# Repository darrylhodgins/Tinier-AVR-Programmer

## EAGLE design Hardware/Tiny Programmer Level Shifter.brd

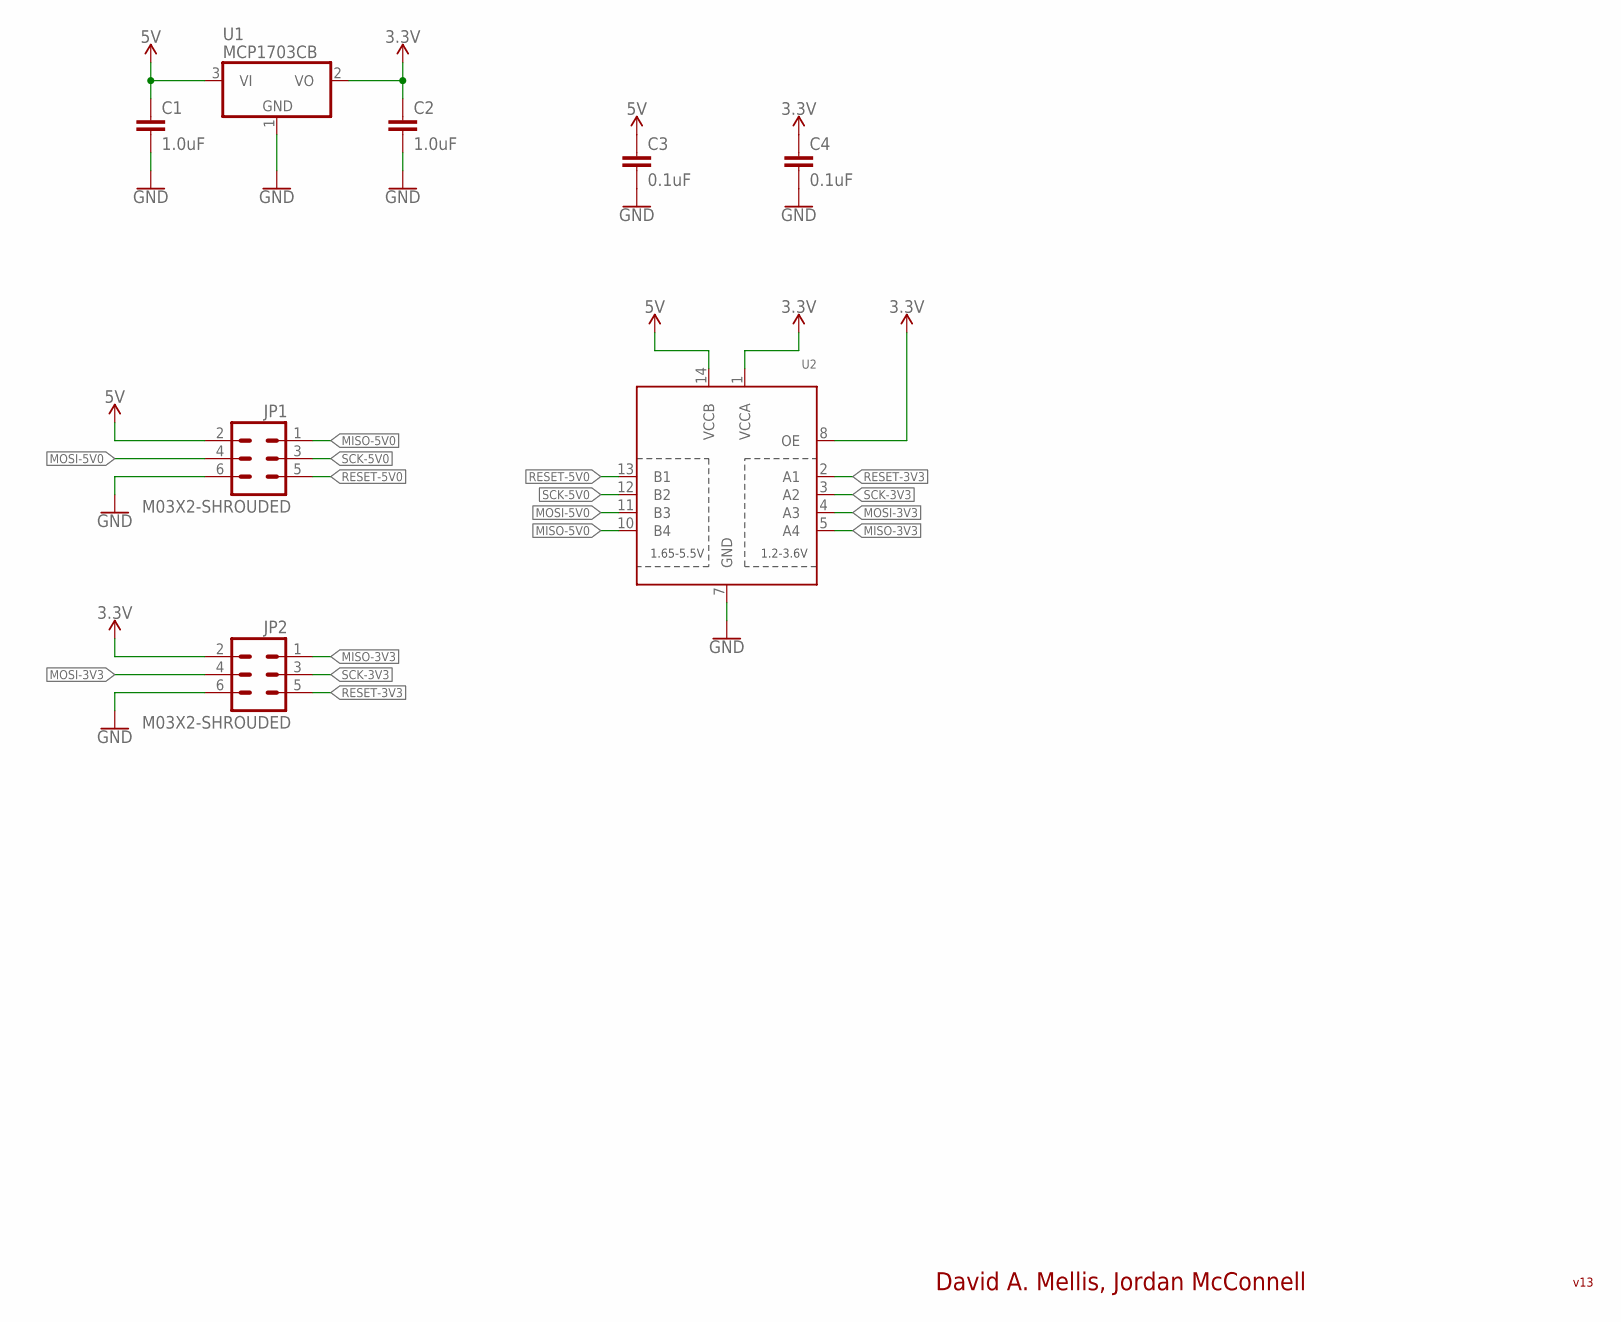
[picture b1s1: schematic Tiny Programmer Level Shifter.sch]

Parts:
C1, C2: 1.0uF; 0603-CAP
C3, C4: 0.1uF; 0603-CAP
JP1, JP2: M03X2-SHROUDED; 2X3-SHROUDED-B
U1: MCP1703CB; SOT23
U2: TXB0104PWR; TSSOP14

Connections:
3.3V: C2.1, C4.1, JP2.2, U1.2 (VO), U2.1 (VCCA), U2.8 (OE)
5V: C1.1, C3.1, JP1.2, U1.3 (VI), U2.14 (VCCB)
GND: C1.2, C2.2, C3.2, C4.2, JP1.6, JP2.6, U1.1 (GND), U2.7 (GND)
MISO-3V3: JP2.1, U2.5 (A4)
MISO-5V0: JP1.1, U2.10 (B4)
MOSI-3V3: JP2.4, U2.4 (A3)
MOSI-5V0: JP1.4, U2.11 (B3)
RESET-3V3: JP2.5, U2.2 (A1)
RESET-5V0: JP1.5, U2.13 (B1)
SCK-3V3: JP2.3, U2.3 (A2)
SCK-5V0: JP1.3, U2.12 (B2)

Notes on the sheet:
David A. Mellis, Jordan McConnell
v13

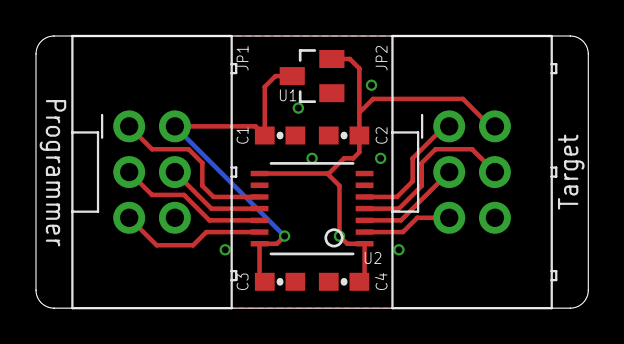
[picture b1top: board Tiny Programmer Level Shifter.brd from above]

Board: 2 copper layers, 30.7 x 15.1 mm, 8 parts (0 on the bottom side), 11 nets.

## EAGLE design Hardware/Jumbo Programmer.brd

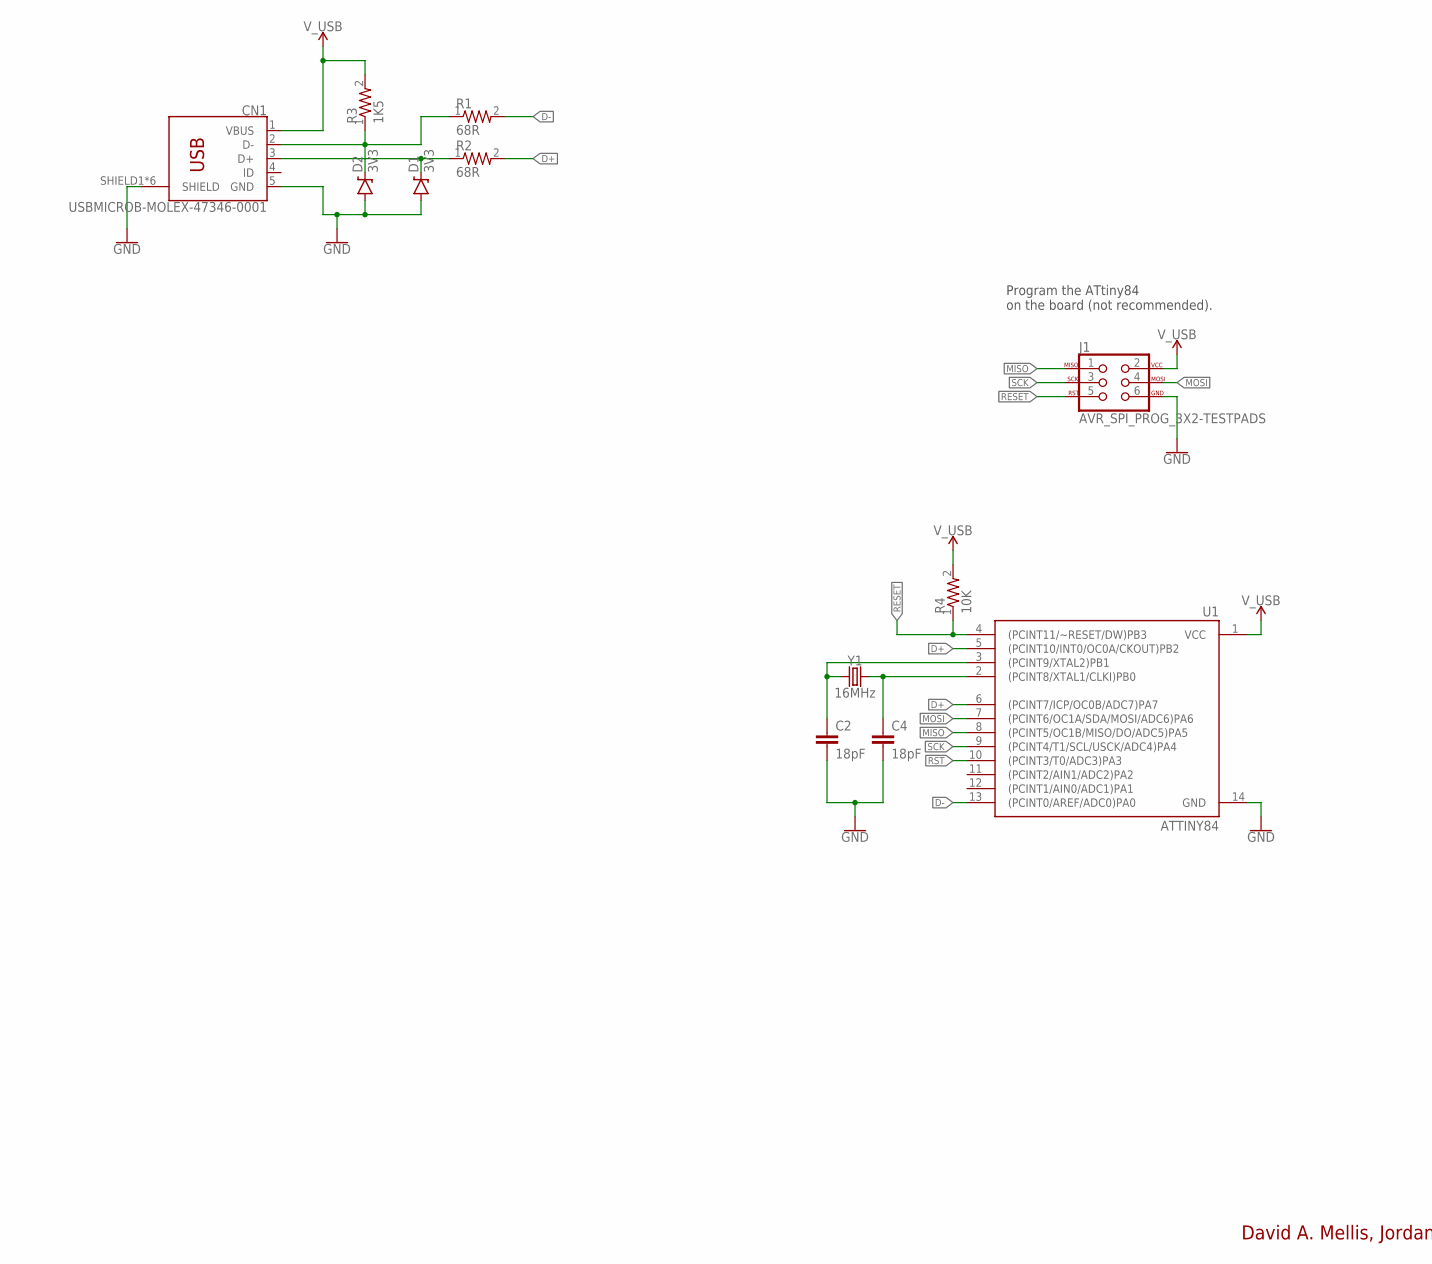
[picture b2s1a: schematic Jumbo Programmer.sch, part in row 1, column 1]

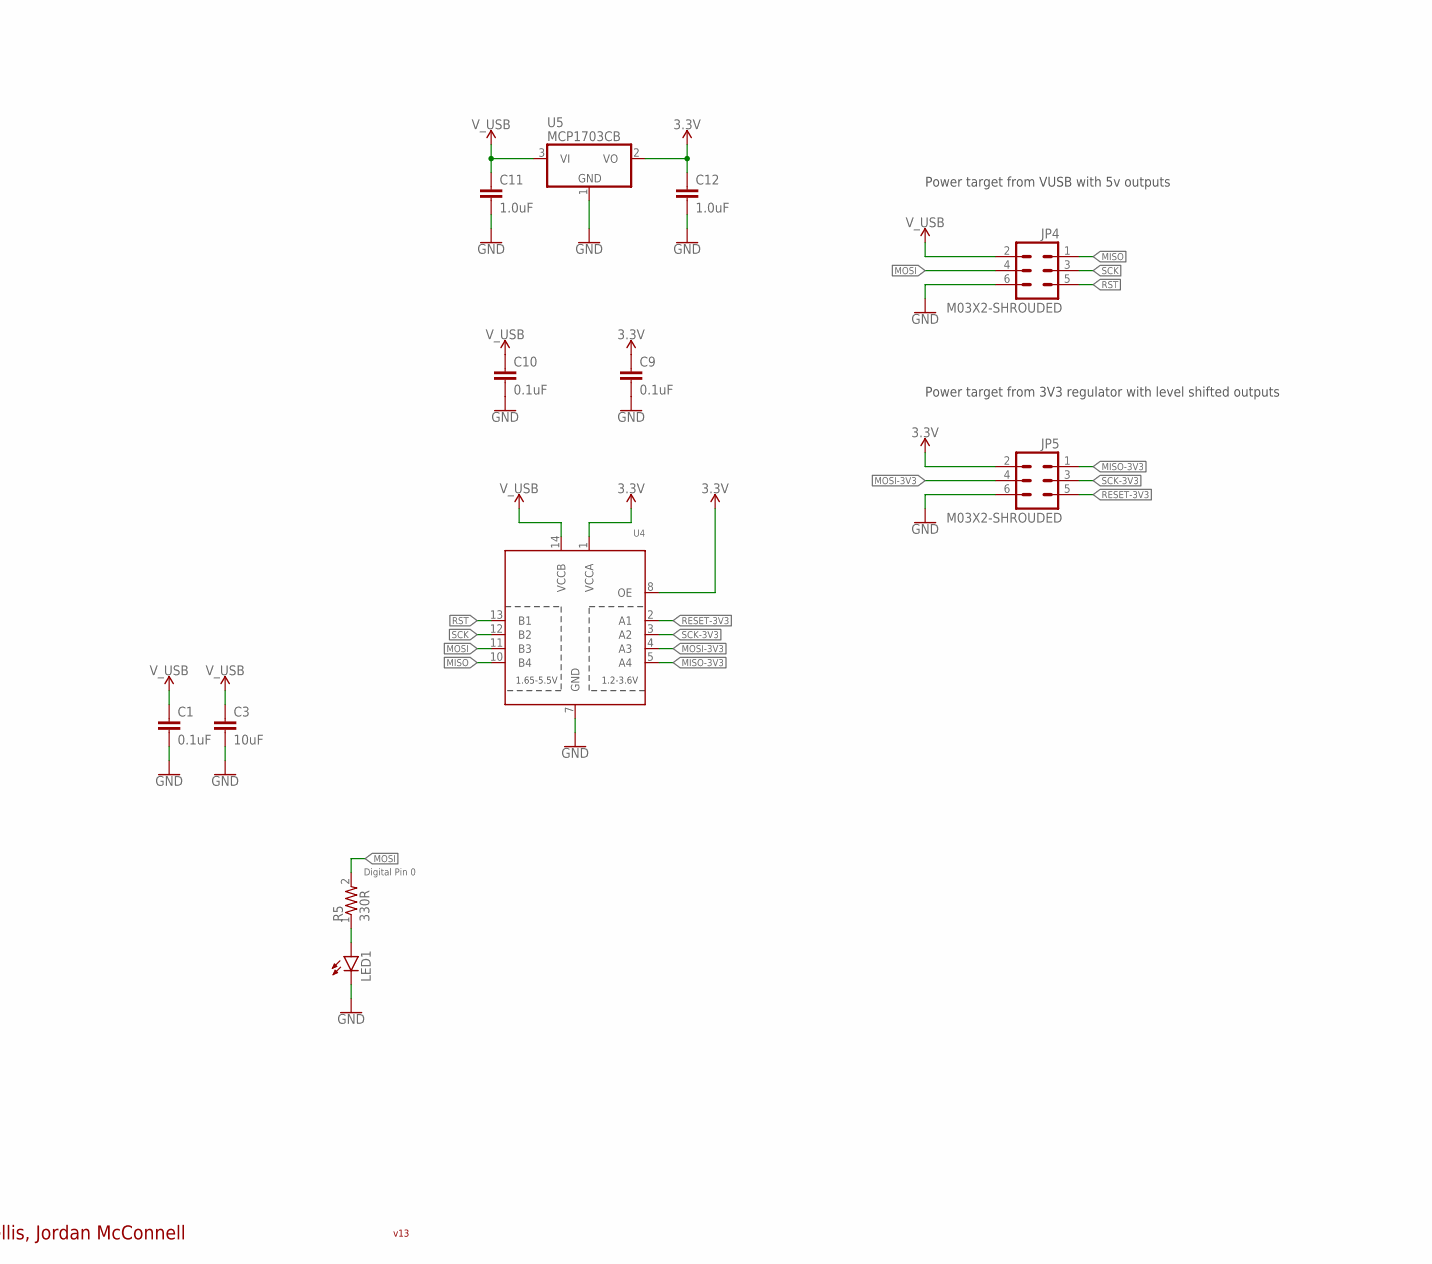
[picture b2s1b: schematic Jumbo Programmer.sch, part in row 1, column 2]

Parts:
C1, C9, C10: 0.1uF; 0603-CAP
C2, C4: 18pF; 0603-CAP
C3: 10uF; 0603-CAP
C11, C12: 1.0uF; 0603-CAP
CN1: USBMICROB-MOLEX-47346-0001; MOLEX_47346-0001
D1, D2: 3V3; SOD-323
J1: AVR_SPI_PROG_3X2-TESTPADS; 2X3_TEST_PADS
JP4, JP5: M03X2-SHROUDED; 2X3-SHROUDED-B
LED1: LED0603; LED-0603
R1, R2: 68R; 0603-RES
R3: 1K5; 0603-RES
R4: 10K; 0603-RES
R5: 330R; 0603-RES
U1: ATTINY84; SO14
U4: TXB0104PWR; TSSOP14
U5: MCP1703CB; SOT23
Y1: 16MHz; CRYSTAL-SMD-5X3.2-4PAD

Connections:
3.3V: C9.1, C12.1, JP5.2, U4.1 (VCCA), U4.8 (OE), U5.2 (VO)
D+: R2.2, U1.5 ((PCINT10/INT0/OC0A/CKOUT)PB2), U1.6 ((PCINT7/ICP/OC0B/ADC7)PA7)
D-: R1.2, U1.13 ((PCINT0/AREF/ADC0)PA0)
GND: C1.2, C2.2, C3.2, C4.2, C9.2, C10.2, C11.2, C12.2, CN1.5 (GND), CN1.SHIELD1 (SHIELD), CN1.SHIELD2 (SHIELD), CN1.SHIELD3 (SHIELD), CN1.SHIELD4 (SHIELD), CN1.SHIELD5 (SHIELD), CN1.SHIELD6 (SHIELD), D1.A, D2.A, J1.6, JP4.6, JP5.6, LED1.C, U1.14 (GND), U4.7 (GND), U5.1 (GND)
MISO: J1.1, JP4.1, U1.8 ((PCINT5/OC1B/MISO/DO/ADC5)PA5), U4.10 (B4)
MISO-3V3: JP5.1, U4.5 (A4)
MOSI: J1.4, JP4.4, R5.2, U1.7 ((PCINT6/OC1A/SDA/MOSI/ADC6)PA6), U4.11 (B3)
MOSI-3V3: JP5.4, U4.4 (A3)
unnamed: CN1.2 (D-), D2.C, R1.1, R3.1
unnamed: CN1.3 (D+), D1.C, R2.1
unnamed: C2.1, U1.3 ((PCINT9/XTAL2)PB1), Y1.1
unnamed: C4.1, U1.2 ((PCINT8/XTAL1/CLKI)PB0), Y1.3 (2)
unnamed: LED1.A, R5.1
RESET: J1.5, R4.1, U1.4 ((PCINT11/~RESET/DW)PB3)
RESET-3V3: JP5.5, U4.2 (A1)
RST: JP4.5, U1.10 ((PCINT3/T0/ADC3)PA3), U4.13 (B1)
SCK: J1.3, JP4.3, U1.9 ((PCINT4/T1/SCL/USCK/ADC4)PA4), U4.12 (B2)
SCK-3V3: JP5.3, U4.3 (A2)
V_USB: C1.1, C3.1, C10.1, C11.1, CN1.1 (VBUS), J1.2, JP4.2, R3.2, R4.2, U1.1 (VCC), U4.14 (VCCB), U5.3 (VI)

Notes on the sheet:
David A. Mellis, Jordan McConnell
Digital Pin 0
Program the ATtiny84 on the board (not recommended).
v13
Power target from VUSB with 5v outputs
Power target from 3V3 regulator with level shifted outputs

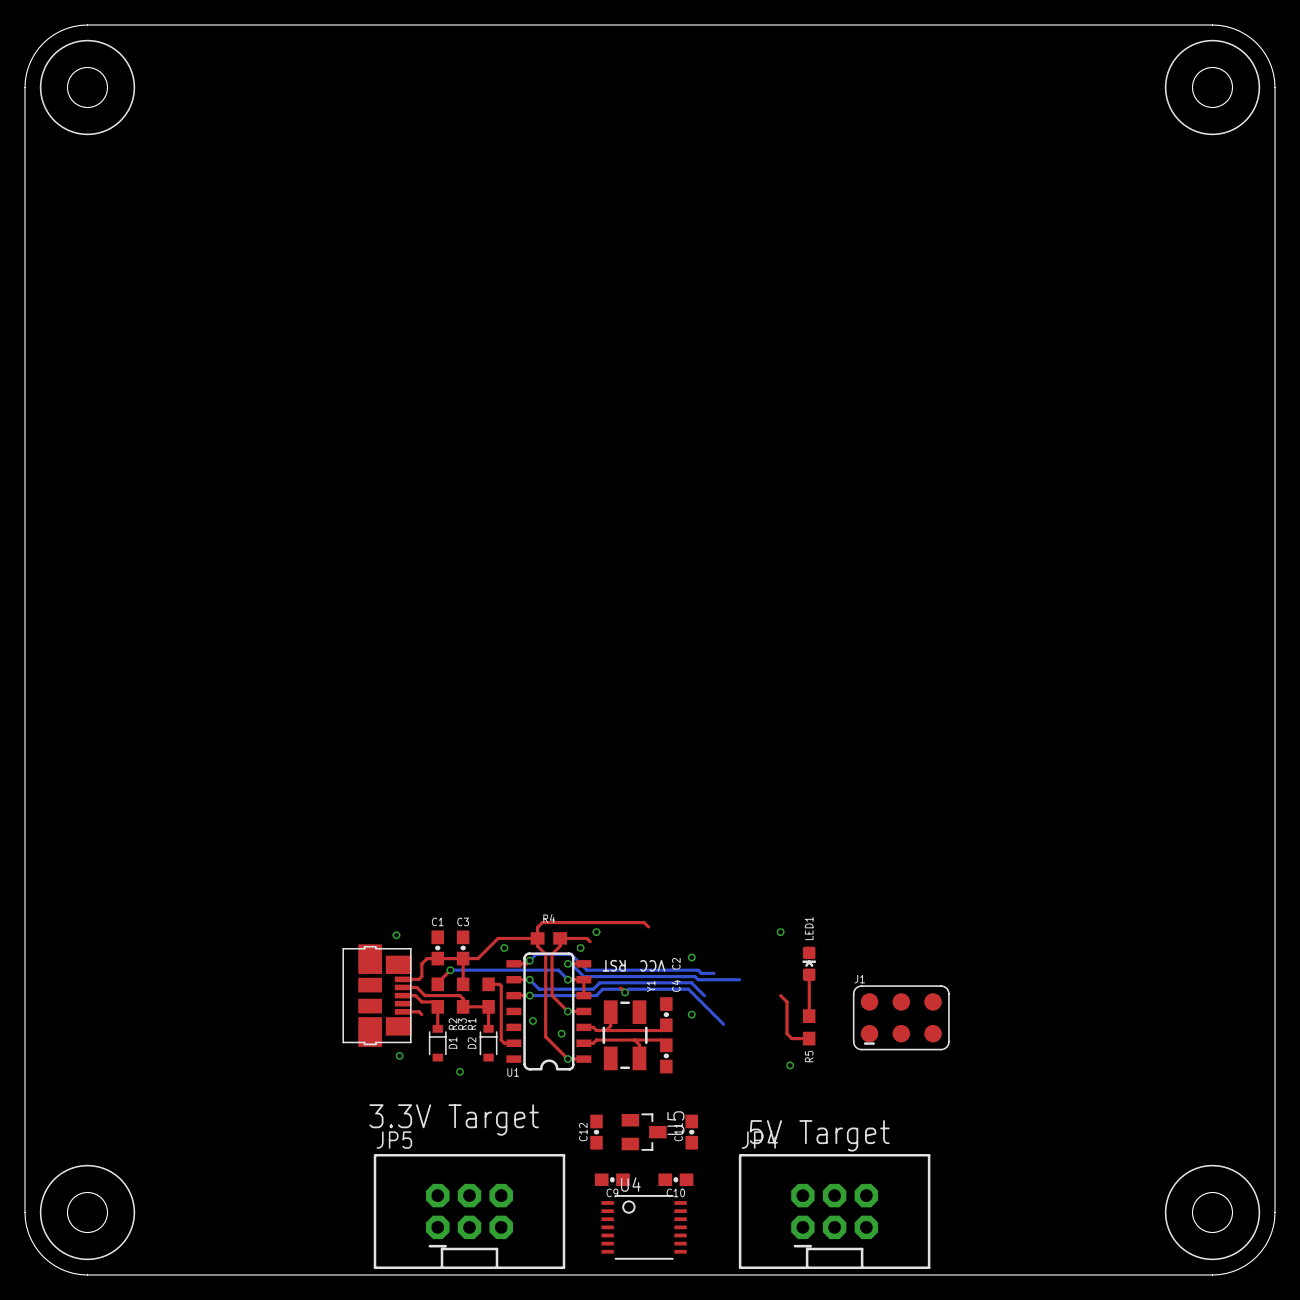
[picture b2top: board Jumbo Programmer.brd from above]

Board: 2 copper layers, 100.0 x 100.0 mm, 25 parts (0 on the bottom side), 19 nets.

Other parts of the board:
PCB1: 10X10CM

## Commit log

2016-04-25 Removed ATTINY85 socket & headers. Replaced USB A plug with USB Micro B socket. Shrinkified board layout. Added shrouded 6-pin ISP header.
2019-07-14 replace USB port, and redraw board
2019-12-09 feat: add jumbo programmer
2019-12-09 feat: add level shifter

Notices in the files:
parts and their libraries:
SparkFun-DigitalIC: Licensing: CC v3.0 Share-Alike You are welcome to use this library for commercial purposes.
SparkFun-Clocks: Licensing: Creative Commons ShareAlike 4.0 International - https://creativecommons.org/licenses/by-sa/4.0
